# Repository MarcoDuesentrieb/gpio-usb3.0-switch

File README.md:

# gpio-usb3.0-switch
KiCad Project for the GPIO-UBS3.0-Switch

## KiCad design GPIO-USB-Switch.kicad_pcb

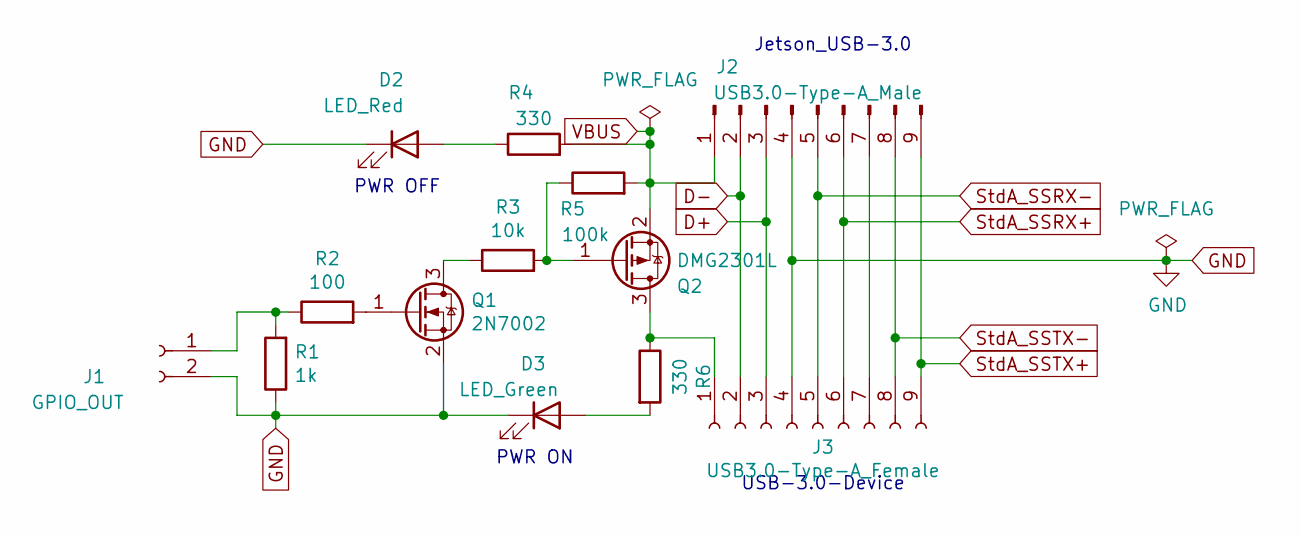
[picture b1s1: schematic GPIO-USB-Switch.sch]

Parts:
D2: LED_Red; LED_0603_1608Metric
D3: LED_Green; LED_0603_1608Metric
J1: GPIO_OUT; JST_XH_B2B-XH-A_1x02_P2.50mm_Vertical
J2: USB3.0-Type-A_Male; 692112030100
J3: USB3.0-Type-A_Female; USB3_A_Amphenol_Female_Horizontal
Q1: 2N7002; SOT-23
Q2: DMG2301L; SOT-23
R1: 1k; R_0603_1608Metric
R2: 100; R_0603_1608Metric
R3: 10k; R_0603_1608Metric
R4, R6: 330; R_0603_1608Metric
R5: 100k; R_0603_1608Metric

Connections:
D+: J2.3, J3.3
D-: J2.2, J3.2
GND: D2.1 (K), D3.1 (K), J1.2, J2.4, J3.4, Q1.2 (S), R1.1
unnamed: D2.2 (A), R4.1
unnamed: D3.2 (A), R6.2
unnamed: J1.1, R1.2, R2.1
unnamed: J2.7, J3.7
unnamed: J3.1, Q2.3 (D), R6.1
unnamed: Q1.1 (G), R2.2
unnamed: Q1.3 (D), R3.1
unnamed: Q2.1 (G), R3.2, R5.1
StdA_SSRX+: J2.6, J3.6
StdA_SSRX-: J2.5, J3.5
StdA_SSTX+: J2.9, J3.9
StdA_SSTX-: J2.8, J3.8
VBUS: J2.1, Q2.2 (S), R4.2, R5.2

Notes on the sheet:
Jetson_USB-3.0
USB-3.0-Device
PWR ON
PWR OFF

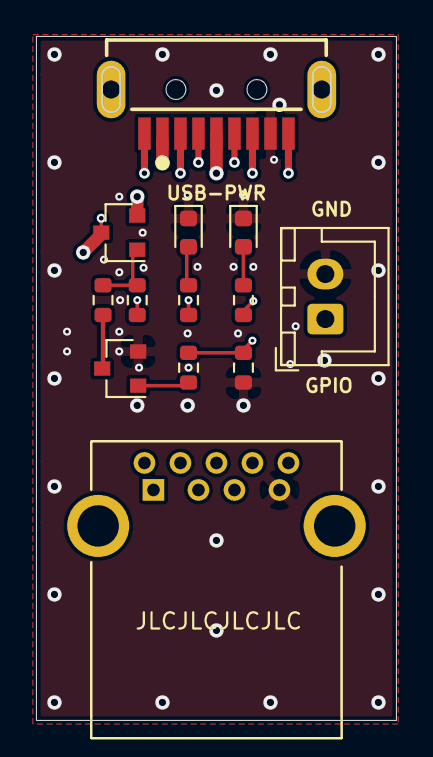
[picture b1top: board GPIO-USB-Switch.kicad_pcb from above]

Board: 4 copper layers, 19.9 x 38.0 mm, 13 parts (0 on the bottom side), 16 nets.

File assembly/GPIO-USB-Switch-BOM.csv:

Designator,Quantity,Value,Footprint,LCSC Part #
"D2,",1,LED_Red,0603,C2286
"D3,",1,LED_Green,0603,C72043
"Q1, ",1,2N7002,SOT-23,C8545
"Q2, ",1,DMG2301L,SOT-23,C10487
"R1, ",1,1k,0603,C21190 
"R2, ",1,100,0603,C22775
"R3, ",1,10k,0603,C25804
"R4, R6, ",2,330,0603,C23138
"R5, ",1,100k,0603,C25803

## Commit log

2021-08-01 added local labels for USB connectors
2021-08-25 finished 4-layer layout!
2021-09-17 4-layer-pcb with blind vias
2021-09-17 changed minimum via size to 0.2mm/0.45mm
